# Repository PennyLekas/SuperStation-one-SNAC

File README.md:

# SuperStation-one-SNAC
THIS PROJECT IS UNTESTED

An experimental SNAC breakout for the Retro Remake SuperStation one.

This project consists of 2 PCBs. One to break the PSX port out into a JST connector and another to receive the borken out PSX control lines and convert them to the USB3.0 SNAC port. 

The SNAC adapter has level shift built in for 5V and 3.3V controllers.

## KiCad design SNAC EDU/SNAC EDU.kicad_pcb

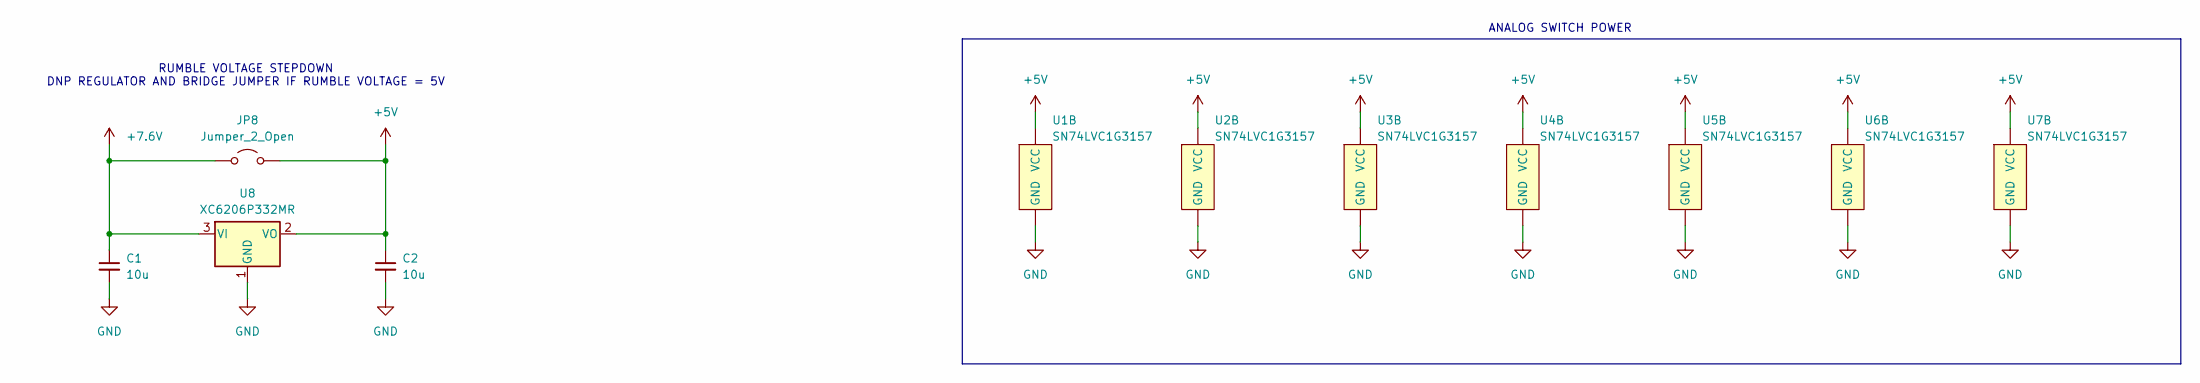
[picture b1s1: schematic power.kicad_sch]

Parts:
C1, C2: 10u; C_0603_1608Metric
JP8: Jumper_2_Open; SolderJumper-2_P1.3mm_Open_Pad1.0x1.5mm
U1, U2, U3, U4, U5, U6, U7: SN74LVC1G3157; TSOT-23-6
U8: XC6206P332MR; SOT-23-3

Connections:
+5V: C2.1, JP8.2 (B), U1.5 (VCC), U2.5 (VCC), U3.5 (VCC), U4.5 (VCC), U5.5 (VCC), U6.5 (VCC), U7.5 (VCC), U8.2 (VO); also elsewhere on the board
+7.6V: C1.1, JP8.1 (A), U8.3 (VI); also elsewhere on the board
GND: C1.2, C2.2, U1.2 (GND), U2.2 (GND), U3.2 (GND), U4.2 (GND), U5.2 (GND), U6.2 (GND), U7.2 (GND), U8.1 (GND); also elsewhere on the board

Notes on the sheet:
RUMBLE VOLTAGE STEPDOWN DNP REGULATOR AND BRIDGE JUMPER IF RUMBLE VOLTAGE = 5V
ANALOG SWITCH POWER

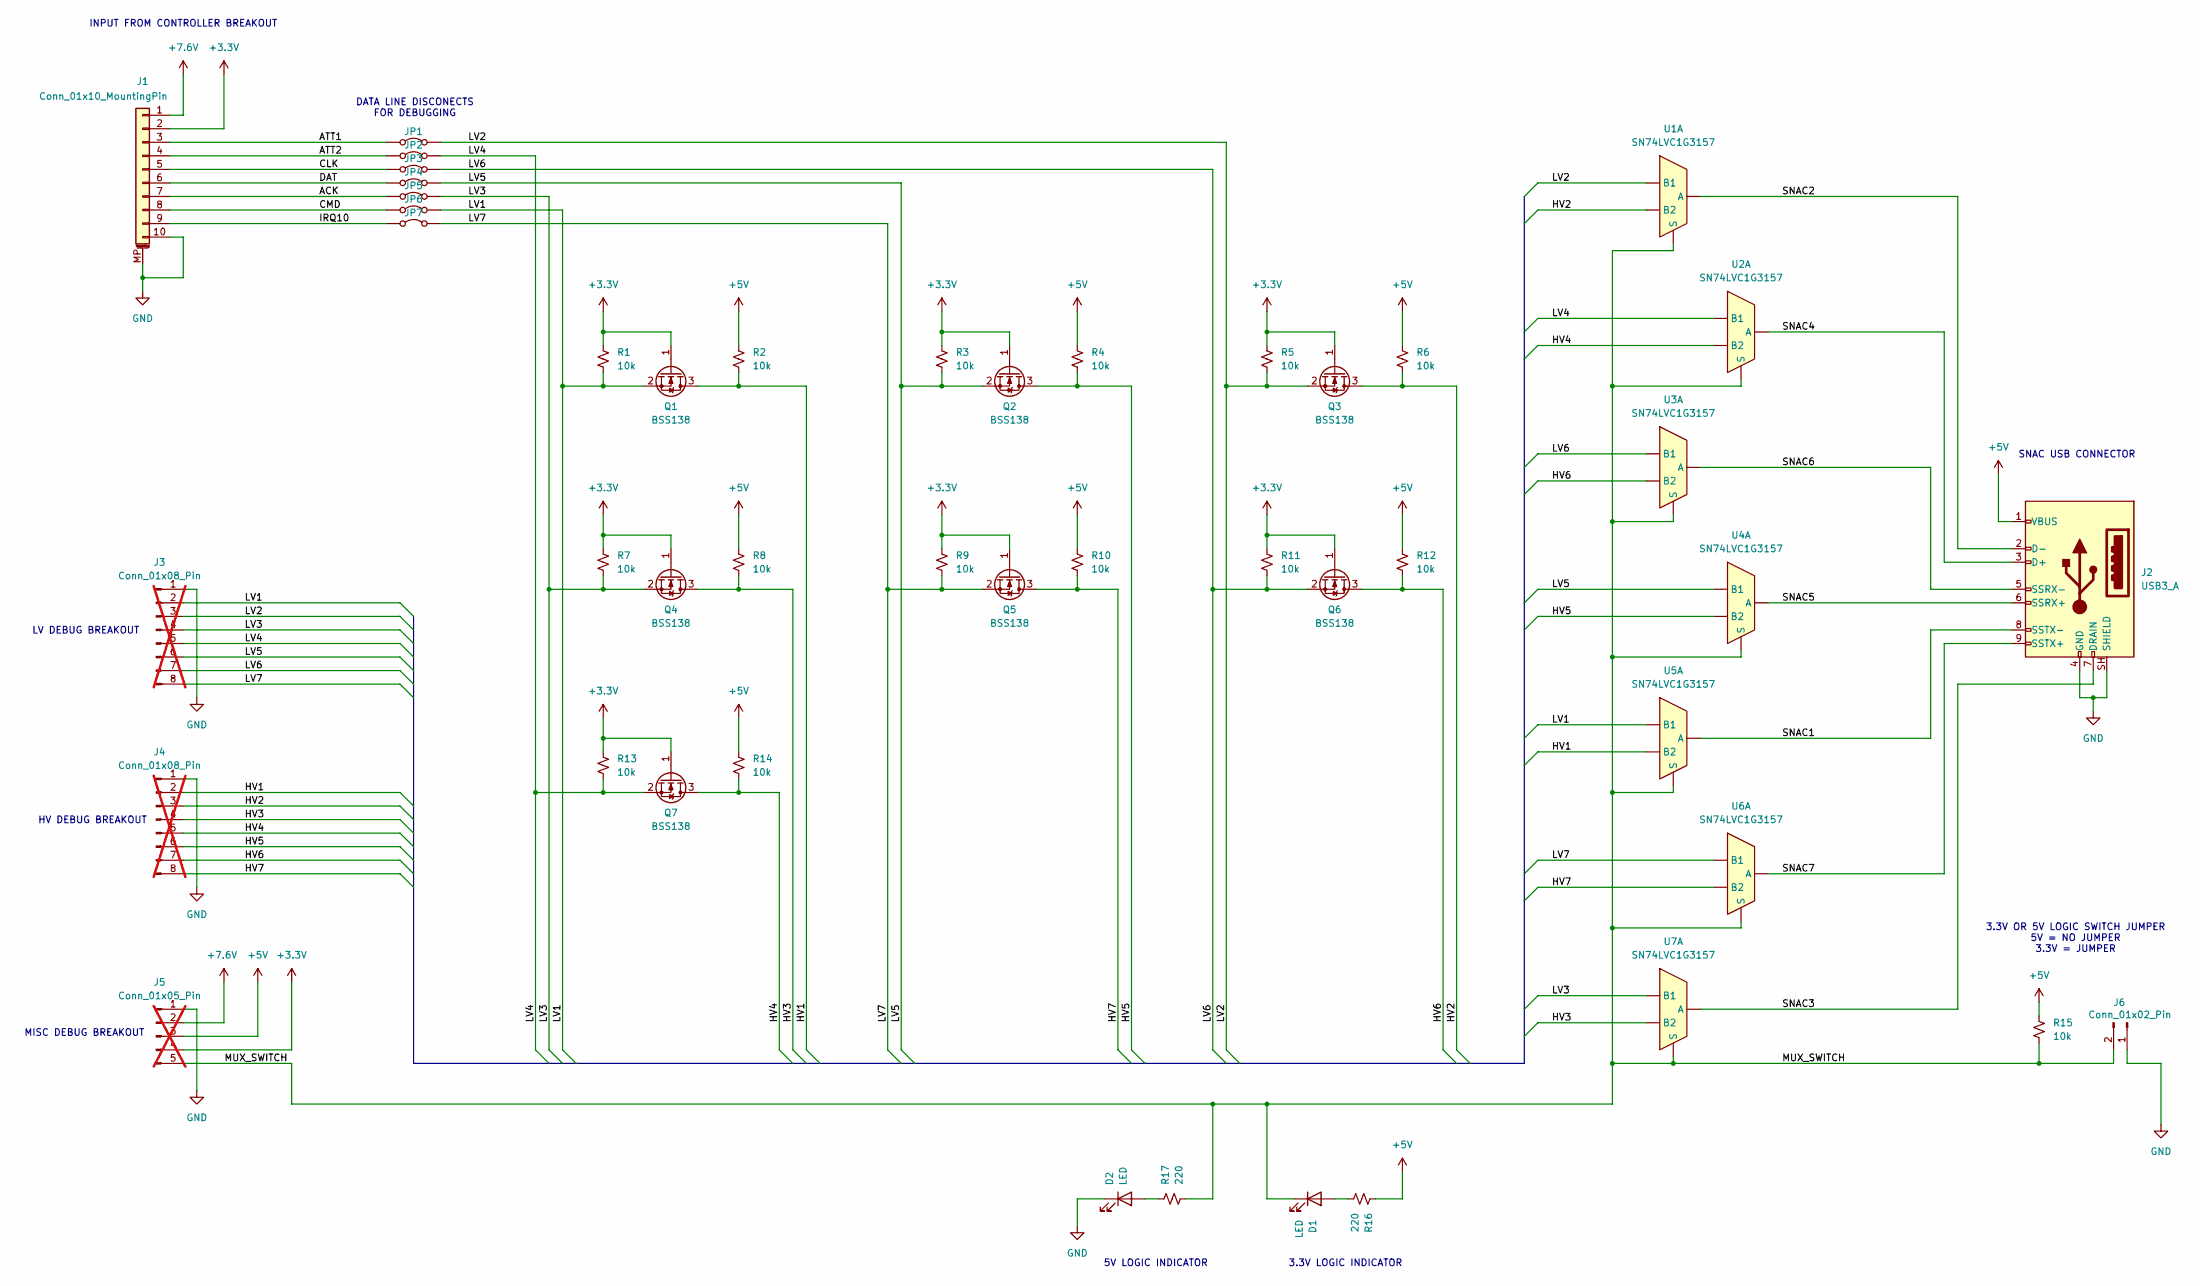
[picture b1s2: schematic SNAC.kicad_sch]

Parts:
D1, D2: LED; LED_0603_1608Metric
J1: Conn_01x10_MountingPin; JST_PH_S10B-PH-SM4-TB_1x10-1MP_P2.00mm_Horizontal
J2: USB3_A; USB3_A_Receptacle_Wuerth_692122030100
J3, J4: Conn_01x08_Pin; PinHeader_1x08_P2.54mm_Vertical; not fitted
J5: Conn_01x05_Pin; PinHeader_1x05_P2.54mm_Vertical; not fitted
J6: Conn_01x02_Pin; PinHeader_1x02_P2.54mm_Vertical
JP1, JP2, JP3, JP4, JP5, JP6, JP7: Jumper_2_Bridged; SolderJumper-2_P1.3mm_Bridged_Pad1.0x1.5mm
Q1, Q2, Q3, Q4, Q5, Q6, Q7: BSS138; SOT-23
R1, R2, R3, R4, R5, R6, R7, R8, R9, R10, R11, R12, R13, R14, R15: 10k; R_0603_1608Metric
R16, R17: 220; R_0603_1608Metric
U1, U2, U3, U4, U5, U6, U7: SN74LVC1G3157; TSOT-23-6

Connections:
+3.3V: J1.2, J5.4, Q1.1 (G), Q2.1 (G), Q3.1 (G), Q4.1 (G), Q5.1 (G), Q6.1 (G), Q7.1 (G), R1.1, R3.1, R5.1, R7.1, R9.1, R11.1, R13.1
+5V: J2.1 (VBUS), J5.3, R2.1, R4.1, R6.1, R8.1, R10.1, R12.1, R14.1, R15.2, R16.1; also elsewhere on the board
+7.6V: J1.1, J5.2; also elsewhere on the board
/SNAC/ACK: J1.7, JP5.1 (A)
/SNAC/ATT1: J1.3, JP1.1 (A)
/SNAC/ATT2: J1.4, JP2.1 (A)
/SNAC/CLK: J1.5, JP3.1 (A)
/SNAC/CMD: J1.8, JP6.1 (A)
/SNAC/DAT: J1.6, JP4.1 (A)
/SNAC/HV1: J4.2, Q1.3 (D), R2.2, U5.1 (B2)
/SNAC/HV2: J4.3, Q3.3 (D), R6.2, U1.1 (B2)
/SNAC/HV3: J4.4, Q4.3 (D), R8.2, U7.1 (B2)
/SNAC/HV4: J4.5, Q7.3 (D), R14.2, U2.1 (B2)
/SNAC/HV5: J4.6, Q2.3 (D), R4.2, U4.1 (B2)
/SNAC/HV6: J4.7, Q6.3 (D), R12.2, U3.1 (B2)
/SNAC/HV7: J4.8, Q5.3 (D), R10.2, U6.1 (B2)
/SNAC/IRQ10: J1.9, JP7.1 (A)
/SNAC/LV1: J3.2, JP6.2 (B), Q1.2 (S), R1.2, U5.3 (B1)
/SNAC/LV2: J3.3, JP1.2 (B), Q3.2 (S), R5.2, U1.3 (B1)
/SNAC/LV3: J3.4, JP5.2 (B), Q4.2 (S), R7.2, U7.3 (B1)
/SNAC/LV4: J3.5, JP2.2 (B), Q7.2 (S), R13.2, U2.3 (B1)
/SNAC/LV5: J3.6, JP4.2 (B), Q2.2 (S), R3.2, U4.3 (B1)
/SNAC/LV6: J3.7, JP3.2 (B), Q6.2 (S), R11.2, U3.3 (B1)
/SNAC/LV7: J3.8, JP7.2 (B), Q5.2 (S), R9.2, U6.3 (B1)
/SNAC/MUX_SWITCH: D1.1 (K), J5.5, J6.2, R15.1, R17.2, U1.6 (S), U2.6 (S), U3.6 (S), U4.6 (S), U5.6 (S), U6.6 (S), U7.6 (S)
/SNAC/SNAC1: J2.8 (SSTX-), U5.4 (A)
/SNAC/SNAC2: J2.2 (D-), U1.4 (A)
/SNAC/SNAC3: J2.7 (DRAIN), U7.4 (A)
/SNAC/SNAC4: J2.3 (D+), U2.4 (A)
/SNAC/SNAC5: J2.6 (SSRX+), U4.4 (A)
/SNAC/SNAC6: J2.5 (SSRX-), U3.4 (A)
/SNAC/SNAC7: J2.9 (SSTX+), U6.4 (A)
GND: D2.1 (K), J1.10, J1.MP (MountPin), J2.4 (GND), J2.SH (SHIELD), J3.1, J4.1, J5.1, J6.1; also elsewhere on the board
unnamed: D1.2 (A), R16.2
unnamed: D2.2 (A), R17.1

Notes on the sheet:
LV DEBUG BREAKOUT
HV DEBUG BREAKOUT
DATA LINE DISCONECTS FOR DEBUGGING
INPUT FROM CONTROLLER BREAKOUT
SNAC USB CONNECTOR
MISC DEBUG BREAKOUT
3.3V LOGIC INDICATOR
5V LOGIC INDICATOR
3.3V OR 5V LOGIC SWITCH JUMPER 5V = NO JUMPER 3.3V = JUMPER

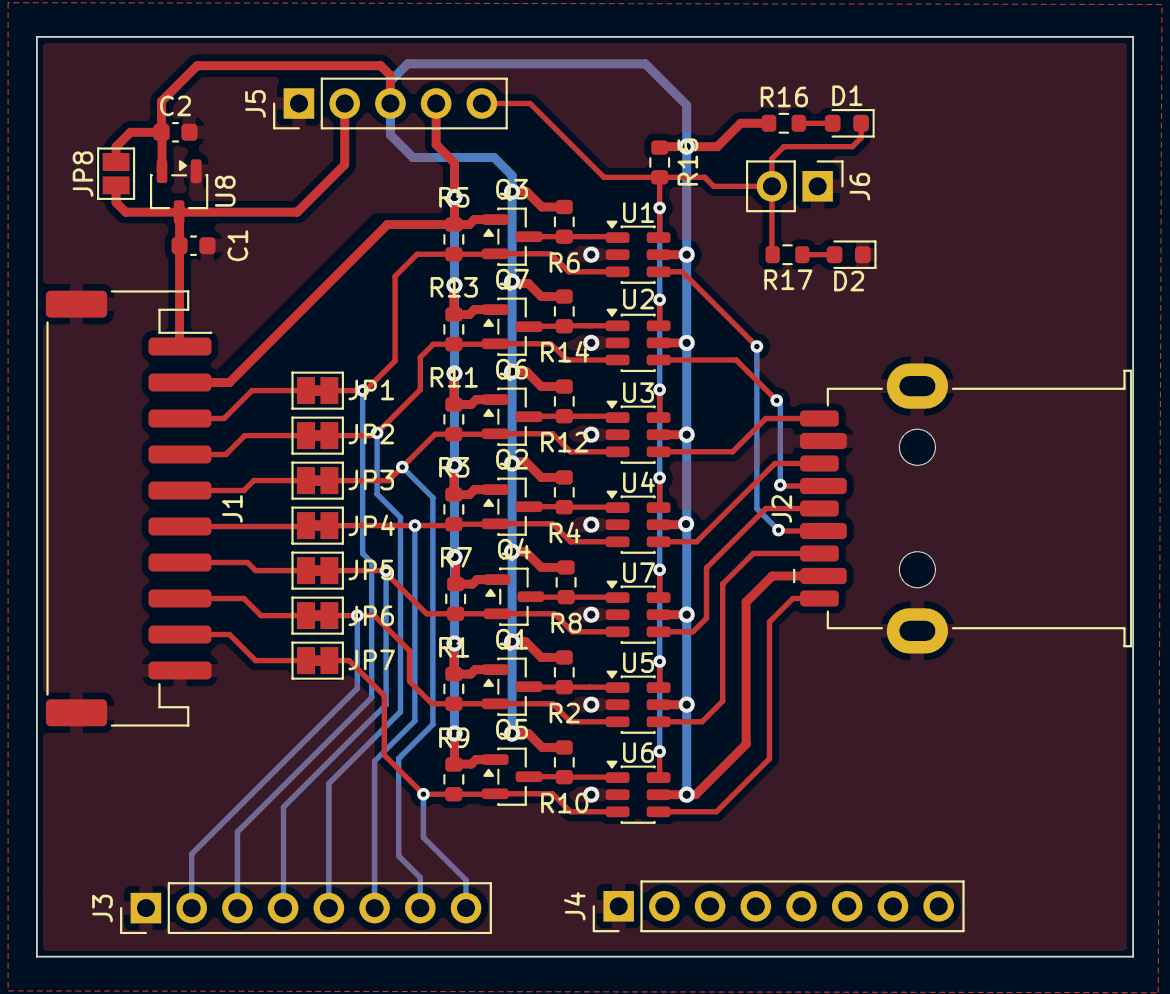
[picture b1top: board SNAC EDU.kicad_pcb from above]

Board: 2 copper layers, 60.9 x 51.1 mm, 50 parts (0 on the bottom side), 35 nets.

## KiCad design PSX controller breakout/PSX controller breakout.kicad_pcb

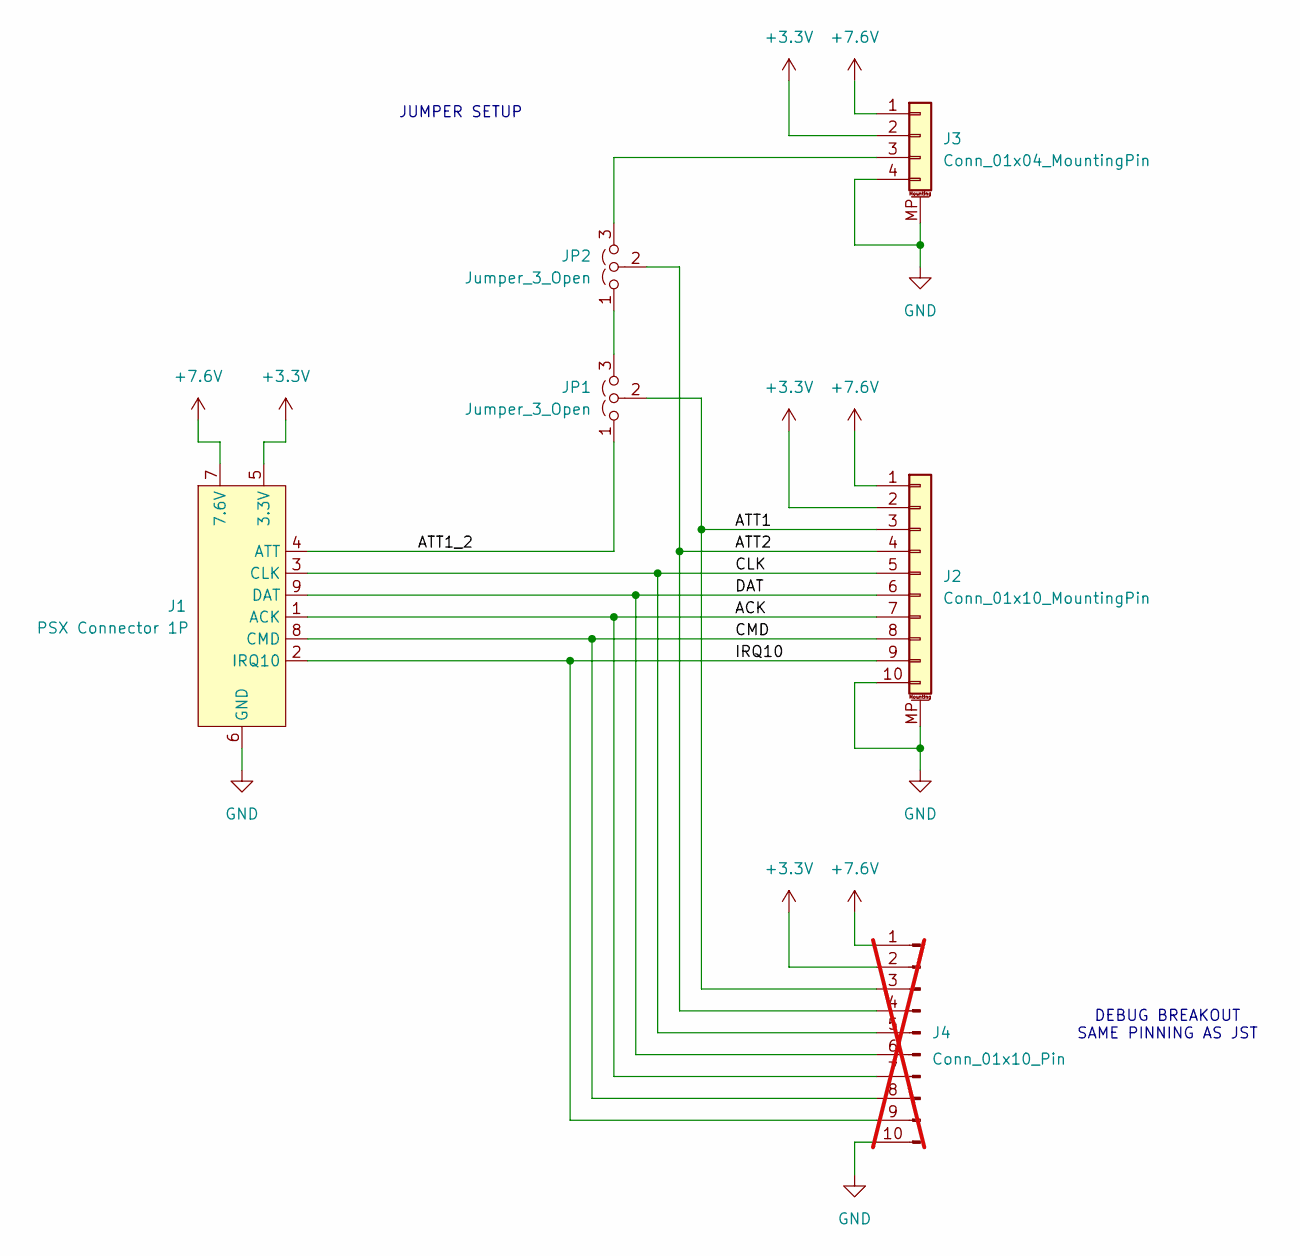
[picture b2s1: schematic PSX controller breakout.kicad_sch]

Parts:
J1: PSX Connector 1P
J2: Conn_01x10_MountingPin; JST_PH_S10B-PH-SM4-TB_1x10-1MP_P2.00mm_Horizontal
J3: Conn_01x04_MountingPin; JST_PH_S4B-PH-SM4-TB_1x04-1MP_P2.00mm_Horizontal
J4: Conn_01x10_Pin; PinSocket_1x10_P2.54mm_Vertical; not fitted
JP1, JP2: Jumper_3_Open; SolderJumper-3_P1.3mm_Open_Pad1.0x1.5mm_NumberLabels

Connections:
+3.3V: J1.5 (3.3V), J2.2, J3.2, J4.2
+7.6V: J1.7 (7.6V), J2.1, J3.1, J4.1
/ACK: J1.1 (ACK), J2.7, J4.7
/ATT1: J2.3, J4.3, JP1.2 (C)
/ATT1_2: J1.4 (ATT), JP1.1 (A)
/ATT2: J2.4, J4.4, JP2.2 (C)
/CLK: J1.3 (CLK), J2.5, J4.5
/CMD: J1.8 (CMD), J2.8, J4.8
/DAT: J1.9 (DAT), J2.6, J4.6
/IRQ10: J1.2 (IRQ10), J2.9, J4.9
GND: J1.6 (GND), J2.10, J2.MP (MountPin), J3.4, J3.MP (MountPin), J4.10
unnamed: J3.3, JP2.3 (B)
unnamed: JP1.3 (B), JP2.1 (A)

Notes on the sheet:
JUMPER SETUP
DEBUG BREAKOUT SAME PINNING AS JST

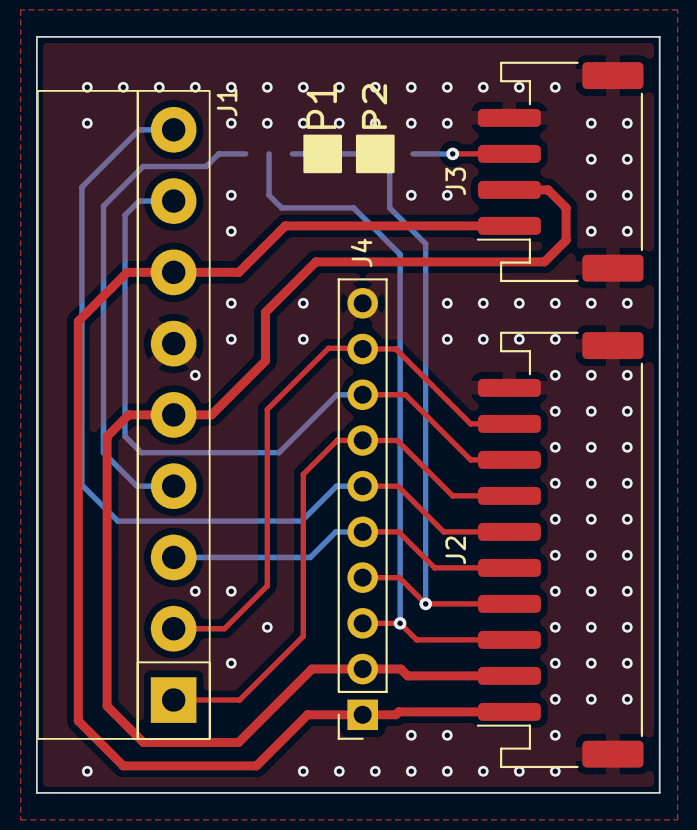
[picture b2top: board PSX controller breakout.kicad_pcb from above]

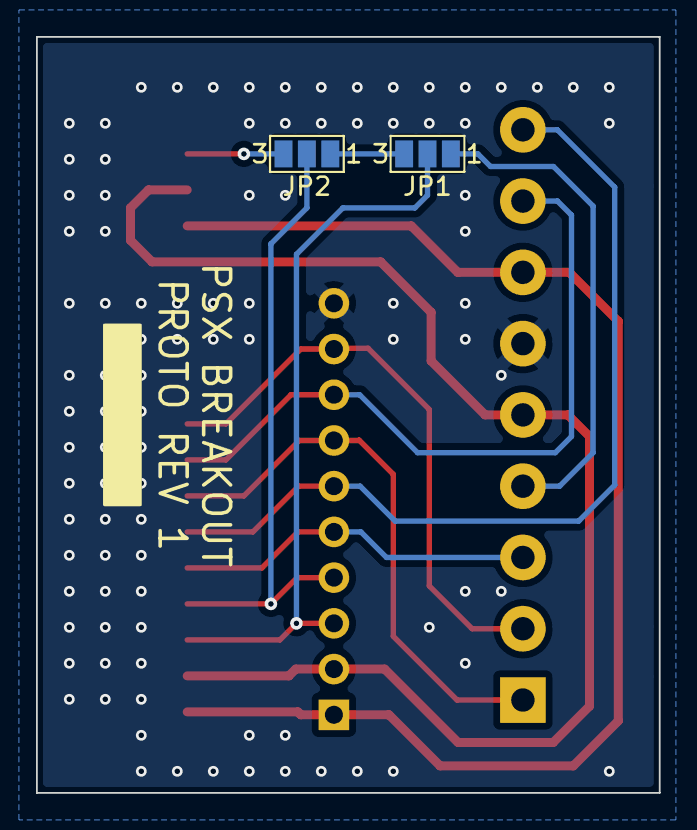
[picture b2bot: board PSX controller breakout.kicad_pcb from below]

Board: 2 copper layers, 34.6 x 42.0 mm, 6 parts (2 on the bottom side), 13 nets.

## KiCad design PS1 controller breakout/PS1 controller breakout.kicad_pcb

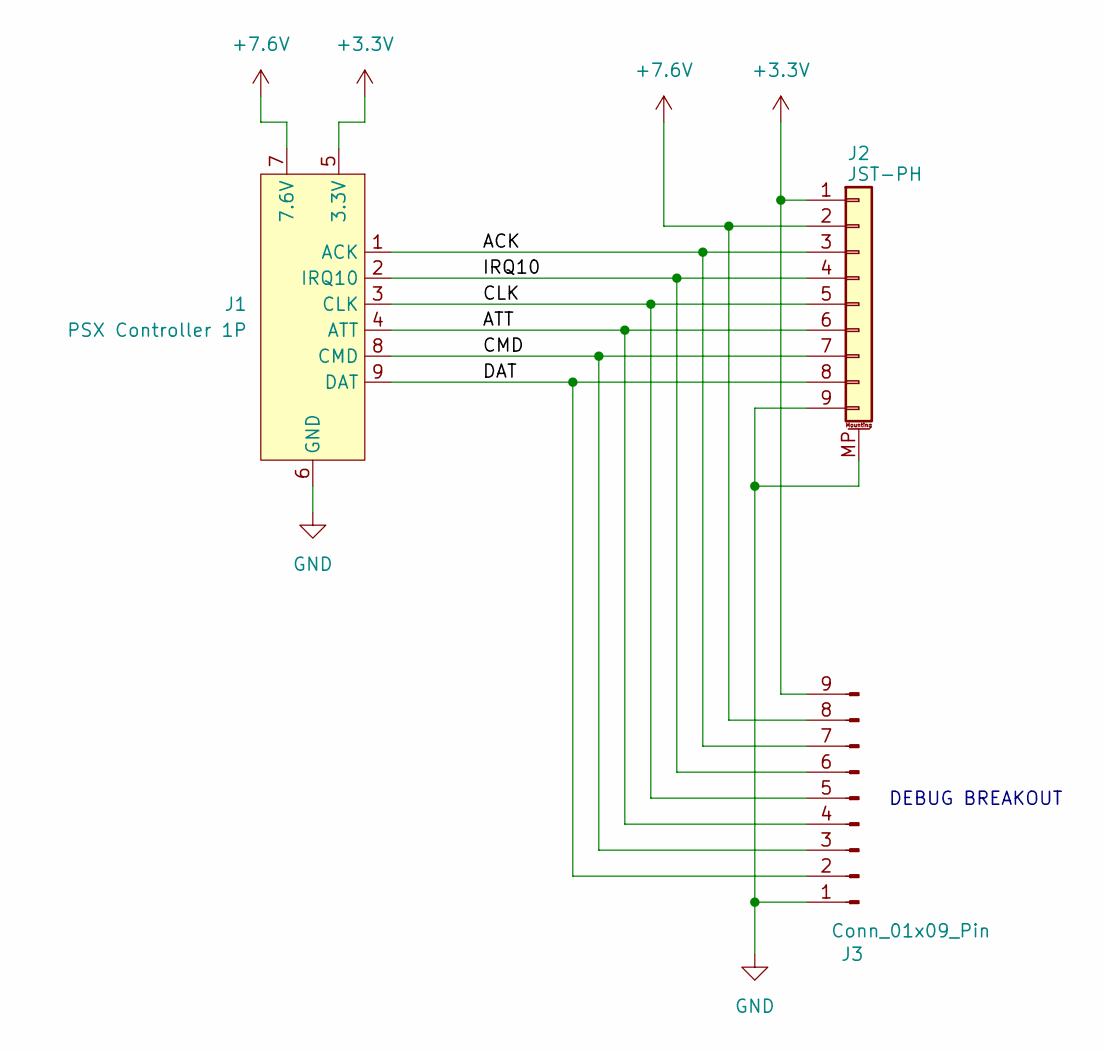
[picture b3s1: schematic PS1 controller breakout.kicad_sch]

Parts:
J1: PSX Controller 1P; PlayStation 1P
J2: JST-PH; JST_PH_S9B-PH-SM4-TB_1x09-1MP_P2.00mm_Horizontal
J3: Conn_01x09_Pin; PinHeader_1x09_P2.54mm_Vertical

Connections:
+3.3V: J1.5 (3.3V), J2.1, J3.9
+7.6V: J1.7 (7.6V), J2.2, J3.8
/ACK: J1.1 (ACK), J2.3, J3.7
/ATT: J1.4 (ATT), J2.6, J3.4
/CLK: J1.3 (CLK), J2.5, J3.5
/CMD: J1.8 (CMD), J2.7, J3.3
/DAT: J1.9 (DAT), J2.8, J3.2
/IRQ10: J1.2 (IRQ10), J2.4, J3.6
GND: J1.6 (GND), J2.9, J2.MP (MountPin), J3.1

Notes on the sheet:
DEBUG BREAKOUT

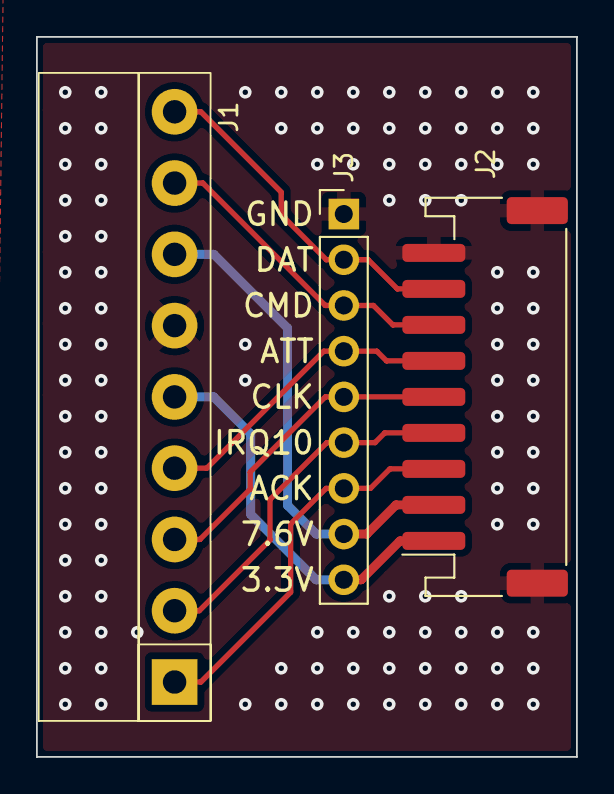
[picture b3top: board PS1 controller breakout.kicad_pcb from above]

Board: 2 copper layers, 30.0 x 40.0 mm, 3 parts (0 on the bottom side), 9 nets.

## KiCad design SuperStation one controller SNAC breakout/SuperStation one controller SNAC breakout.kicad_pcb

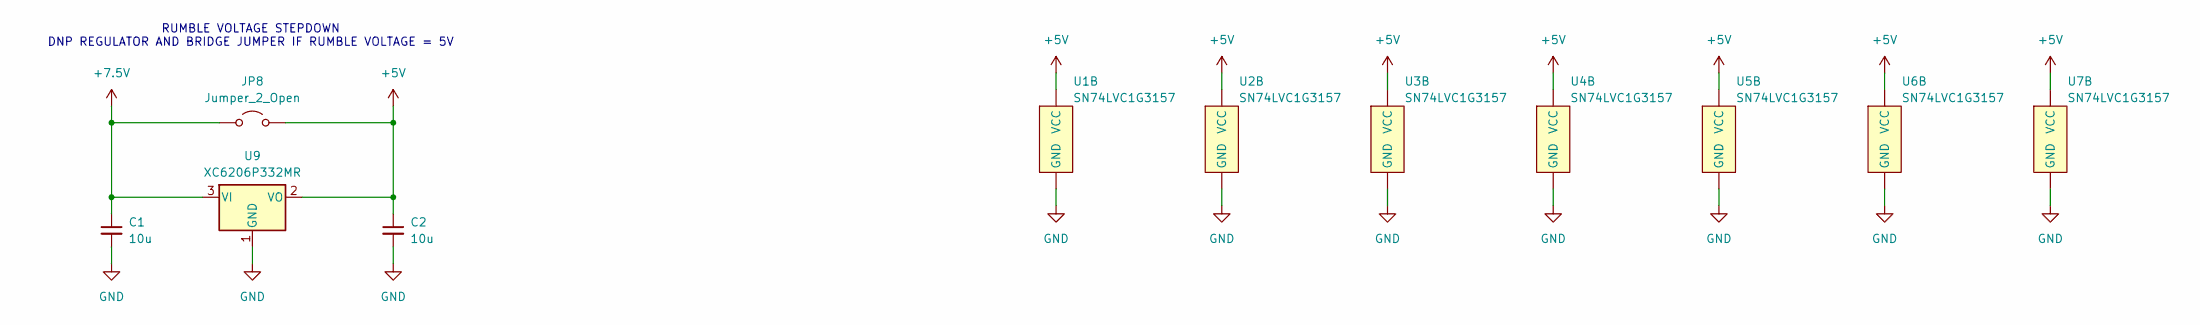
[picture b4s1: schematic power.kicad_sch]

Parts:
C1, C2: 10u; C_0603_1608Metric
JP8: Jumper_2_Open; SolderJumper-2_P1.3mm_Open_Pad1.0x1.5mm
U1, U2, U3, U4, U5, U6, U7: SN74LVC1G3157; TSOT-23-6
U9: XC6206P332MR; SOT-23-3

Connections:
+5V: C2.1, JP8.2 (B), U1.5 (VCC), U2.5 (VCC), U3.5 (VCC), U4.5 (VCC), U5.5 (VCC), U6.5 (VCC), U7.5 (VCC), U9.2 (VO); also elsewhere on the board
+7.5V: C1.1, JP8.1 (A), U9.3 (VI); also elsewhere on the board
GND: C1.2, C2.2, U1.2 (GND), U2.2 (GND), U3.2 (GND), U4.2 (GND), U5.2 (GND), U6.2 (GND), U7.2 (GND), U9.1 (GND); also elsewhere on the board

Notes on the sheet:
RUMBLE VOLTAGE STEPDOWN DNP REGULATOR AND BRIDGE JUMPER IF RUMBLE VOLTAGE = 5V

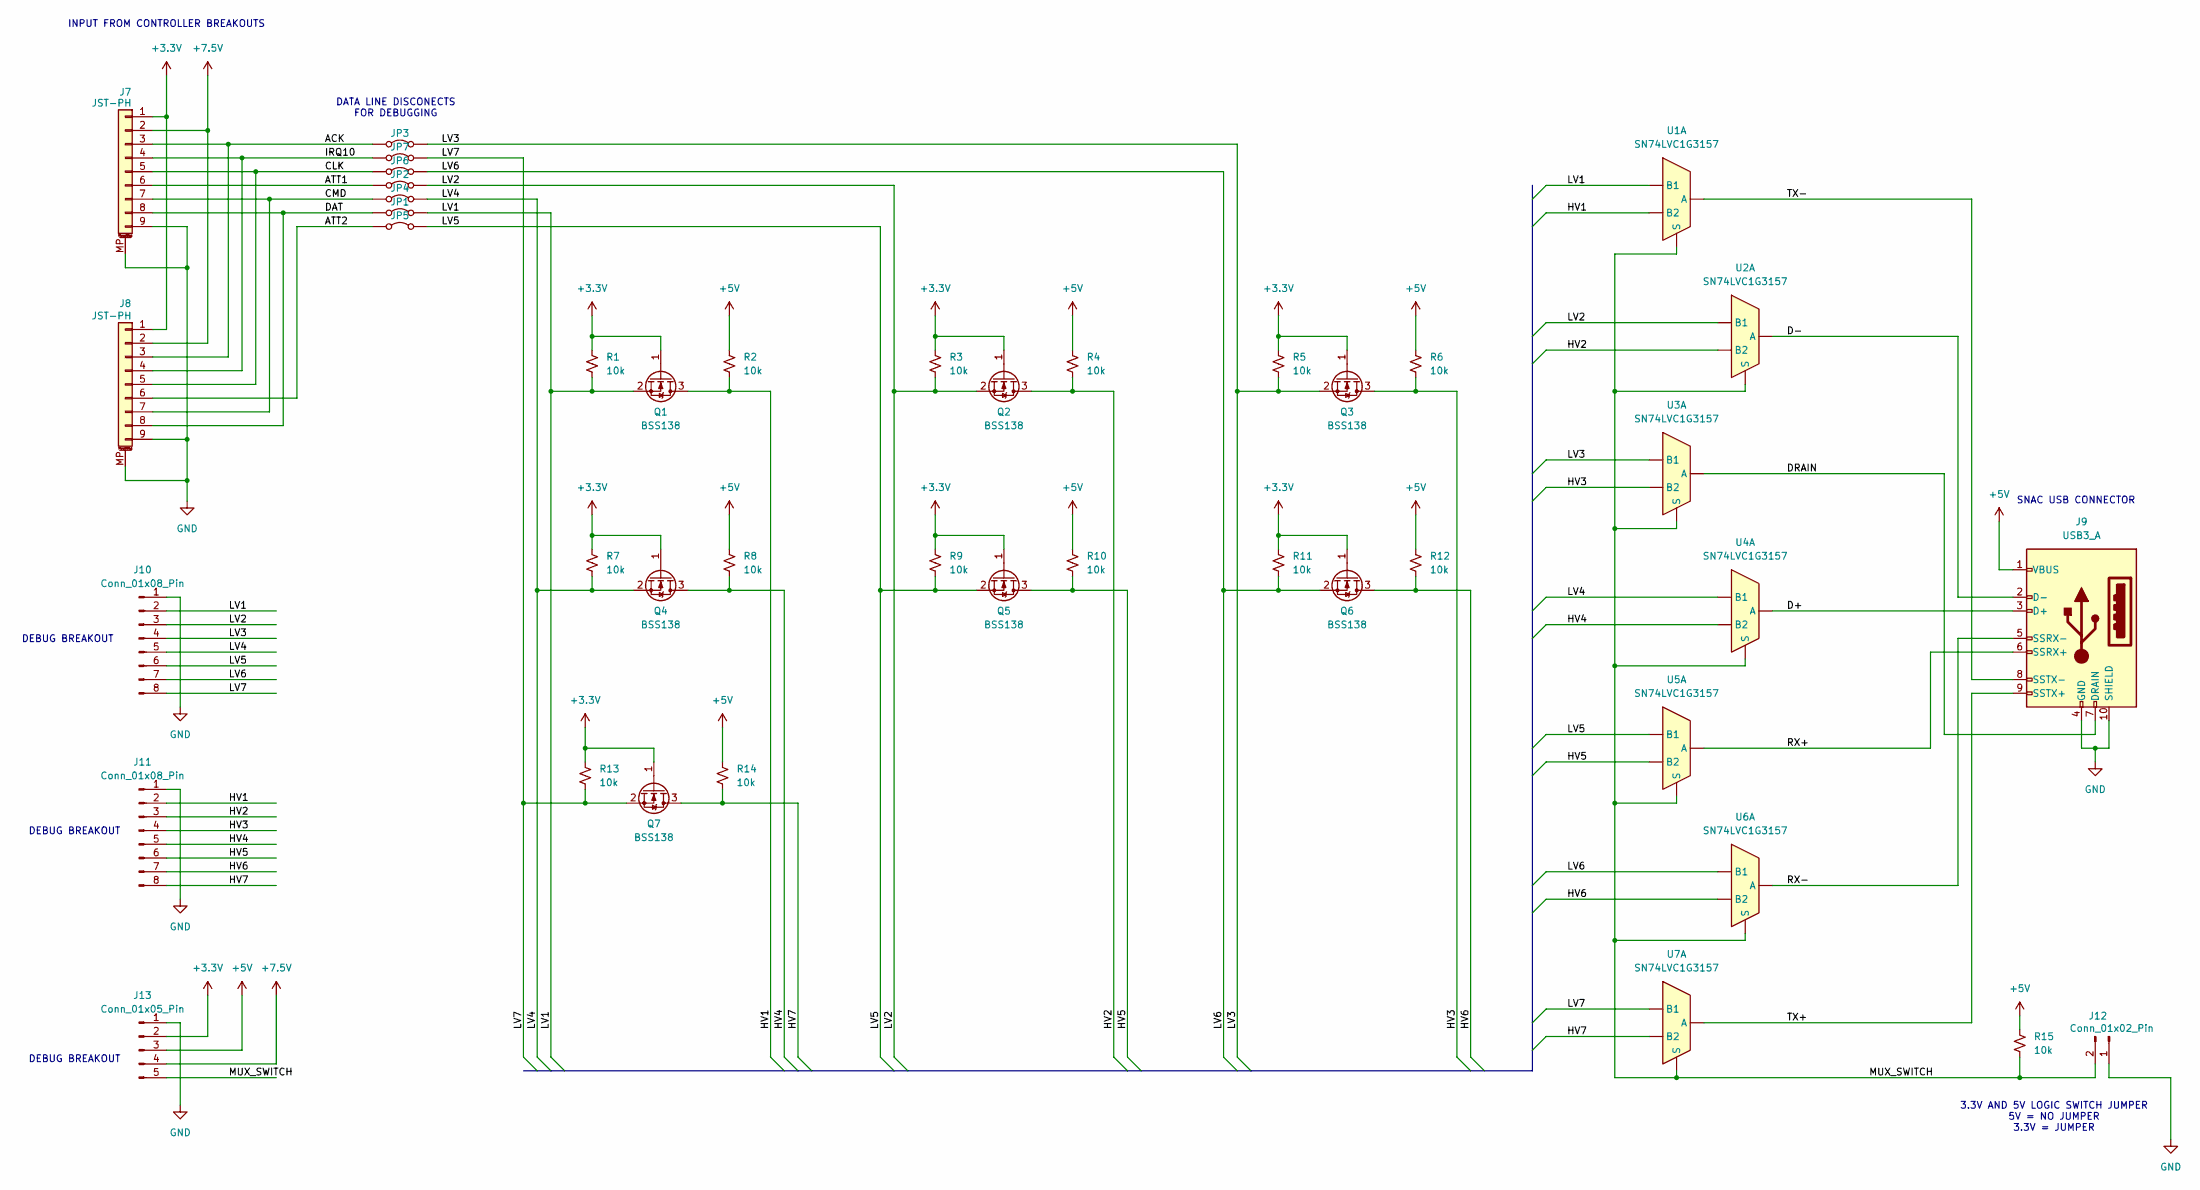
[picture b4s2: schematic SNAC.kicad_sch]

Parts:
J7, J8: JST-PH; JST_PH_S9B-PH-SM4-TB_1x09-1MP_P2.00mm_Horizontal
J9: USB3_A; USB3_A_Receptacle_Wuerth_692122030100
J10, J11: Conn_01x08_Pin; PinHeader_1x08_P2.54mm_Vertical
J12: Conn_01x02_Pin; PinHeader_1x02_P2.54mm_Vertical
J13: Conn_01x05_Pin; PinHeader_1x05_P2.54mm_Vertical
JP1, JP2, JP3, JP4, JP5, JP6, JP7: Jumper_2_Bridged; SolderJumper-2_P1.3mm_Bridged_Pad1.0x1.5mm
Q1, Q2, Q3, Q4, Q5, Q6, Q7: BSS138; SOT-23
R1, R2, R3, R4, R5, R6, R7, R8, R9, R10, R11, R12, R13, R14, R15: 10k; R_0603_1608Metric
U1, U2, U3, U4, U5, U6, U7: SN74LVC1G3157; TSOT-23-6

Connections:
+3.3V: J7.1, J8.1, J13.2, Q1.1 (G), Q2.1 (G), Q3.1 (G), Q4.1 (G), Q5.1 (G), Q6.1 (G), Q7.1 (G), R1.1, R3.1, R5.1, R7.1, R9.1, R11.1, R13.1
+5V: J9.1 (VBUS), J13.3, R2.1, R4.1, R6.1, R8.1, R10.1, R12.1, R14.1, R15.2; also elsewhere on the board
+7.5V: J7.2, J8.2, J13.4; also elsewhere on the board
/SNAC/ACK: J7.3, J8.3, JP3.1 (A)
/SNAC/ATT1: J7.6, JP2.1 (A)
/SNAC/ATT2: J8.6, JP5.1 (A)
/SNAC/CLK: J7.5, J8.5, JP6.1 (A)
/SNAC/CMD: J7.7, J8.7, JP4.1 (A)
/SNAC/D+: J9.3 (D+), U4.4 (A)
/SNAC/D-: J9.2 (D-), U2.4 (A)
/SNAC/DAT: J7.8, J8.8, JP1.1 (A)
/SNAC/DRAIN: J9.7 (DRAIN), U3.4 (A)
/SNAC/HV1: J11.2, Q1.3 (D), R2.2, U1.1 (B2)
/SNAC/HV2: J11.3, Q2.3 (D), R4.2, U2.1 (B2)
/SNAC/HV3: J11.4, Q3.3 (D), R6.2, U3.1 (B2)
/SNAC/HV4: J11.5, Q4.3 (D), R8.2, U4.1 (B2)
/SNAC/HV5: J11.6, Q5.3 (D), R10.2, U5.1 (B2)
/SNAC/HV6: J11.7, Q6.3 (D), R12.2, U6.1 (B2)
/SNAC/HV7: J11.8, Q7.3 (D), R14.2, U7.1 (B2)
/SNAC/IRQ10: J7.4, J8.4, JP7.1 (A)
/SNAC/LV1: J10.2, JP1.2 (B), Q1.2 (S), R1.2, U1.3 (B1)
/SNAC/LV2: J10.3, JP2.2 (B), Q2.2 (S), R3.2, U2.3 (B1)
/SNAC/LV3: J10.4, JP3.2 (B), Q3.2 (S), R5.2, U3.3 (B1)
/SNAC/LV4: J10.5, JP4.2 (B), Q4.2 (S), R7.2, U4.3 (B1)
/SNAC/LV5: J10.6, JP5.2 (B), Q5.2 (S), R9.2, U5.3 (B1)
/SNAC/LV6: J10.7, JP6.2 (B), Q6.2 (S), R11.2, U6.3 (B1)
/SNAC/LV7: J10.8, JP7.2 (B), Q7.2 (S), R13.2, U7.3 (B1)
/SNAC/MUX_SWITCH: J12.2, J13.5, R15.1, U1.6 (S), U2.6 (S), U3.6 (S), U4.6 (S), U5.6 (S), U6.6 (S), U7.6 (S)
/SNAC/RX+: J9.6 (SSRX+), U5.4 (A)
/SNAC/RX-: J9.5 (SSRX-), U6.4 (A)
/SNAC/TX+: J9.9 (SSTX+), U7.4 (A)
/SNAC/TX-: J9.8 (SSTX-), U1.4 (A)
GND: J7.9, J7.MP (MountPin), J8.9, J8.MP (MountPin), J9.4 (GND), J9.10 (SHIELD), J10.1, J11.1, J12.1, J13.1; also elsewhere on the board

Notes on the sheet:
DEBUG BREAKOUT
DATA LINE DISCONECTS FOR DEBUGGING
INPUT FROM CONTROLLER BREAKOUTS
SNAC USB CONNECTOR
3.3V AND 5V LOGIC SWITCH JUMPER 5V = NO JUMPER 3.3V = JUMPER

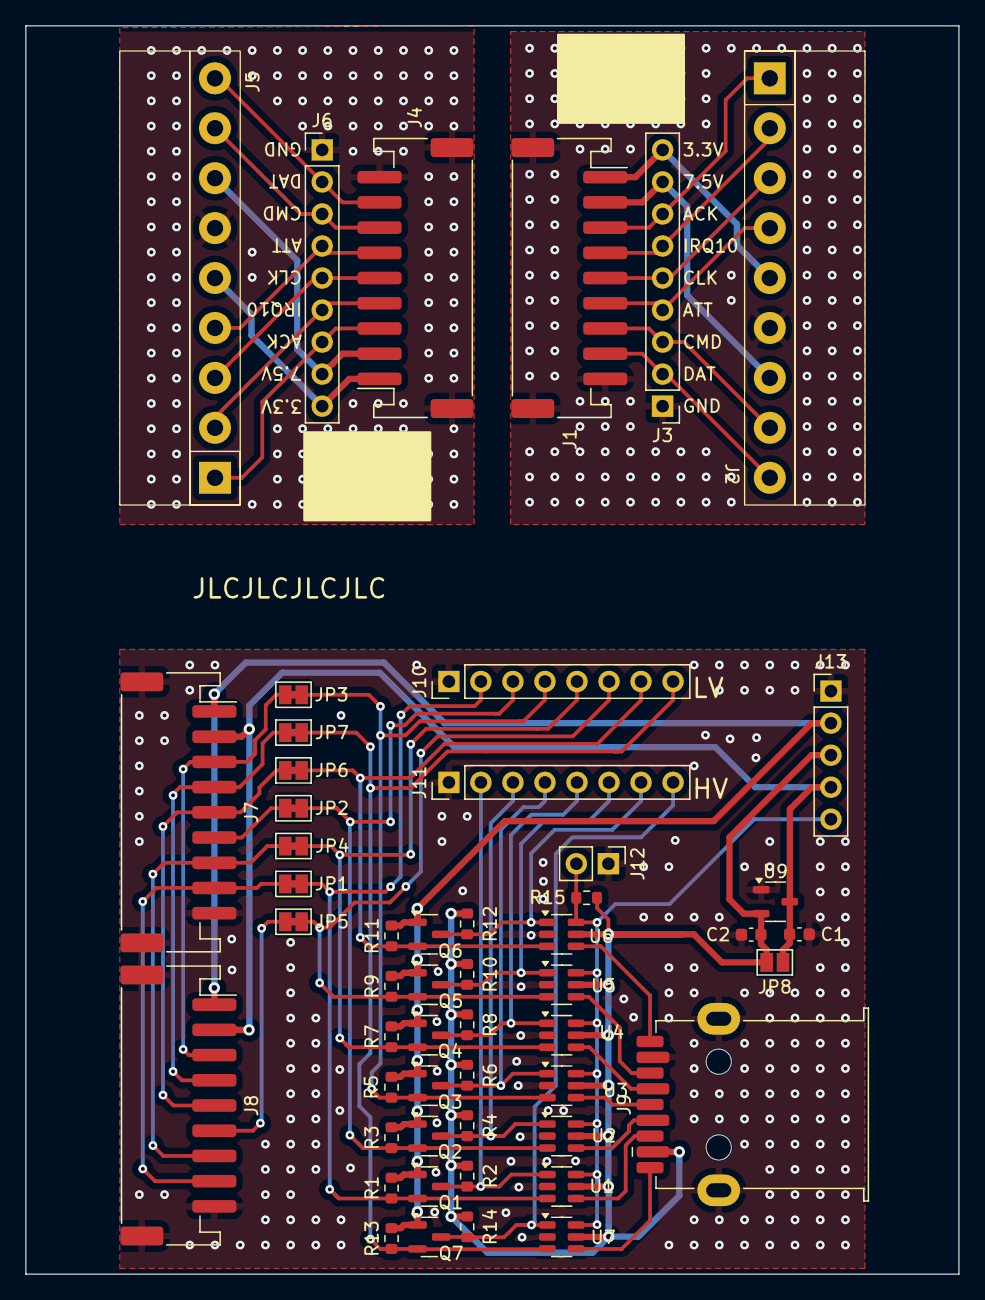
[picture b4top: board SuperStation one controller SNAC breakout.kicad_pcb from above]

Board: 2 copper layers, 74.0 x 99.0 mm, 53 parts (0 on the bottom side), 51 nets.

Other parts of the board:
J1, J4: JST-PH; JST_PH_S9B-PH-SM4-TB_1x09-1MP_P2.00mm_Horizontal
J2, J5: PlayStation Con 1P; PlayStation 1P
J3, J6: Conn_01x09_Pin; PinHeader_1x09_P2.54mm_Vertical

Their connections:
+3.3V_P1: J1.1, J2.5 (3.3V), J3.9
+3.3V_P2: J4.1, J5.5 (3.3V), J6.9
+7.5V_P1: J1.2, J2.7 (7.6V), J3.8
+7.5V_P2: J4.2, J5.7 (7.6V), J6.8
/PS Input Breakout/ACK_P1: J1.3, J2.1 (ACK), J3.7
/PS Input Breakout/ACK_P2: J4.3, J5.1 (ACK), J6.7
/PS Input Breakout/ATT_P1: J1.6, J2.4 (ATT), J3.4
/PS Input Breakout/ATT_P2: J4.6, J5.4 (ATT), J6.4
/PS Input Breakout/CLK_P1: J1.5, J2.3 (CLK), J3.5
/PS Input Breakout/CLK_P2: J4.5, J5.3 (CLK), J6.5
/PS Input Breakout/CMD_P1: J1.7, J2.8 (CMD), J3.3
/PS Input Breakout/CMD_P2: J4.7, J5.8 (CMD), J6.3
/PS Input Breakout/DAT_P1: J1.8, J2.9 (DAT), J3.2
/PS Input Breakout/DAT_P2: J4.8, J5.9 (DAT), J6.2
/PS Input Breakout/IRQ10_P1: J1.4, J2.2 (IRQ10), J3.6
/PS Input Breakout/IRQ10_P2: J4.4, J5.2 (IRQ10), J6.6
GND_P1: J1.9, J1.MP (MountPin), J2.6 (GND), J3.1
GND_P2: J4.9, J4.MP (MountPin), J5.6 (GND), J6.1

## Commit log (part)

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2025-01-28 added reference material
2025-01-28 completed initial schematic and started layout
2025-02-02 continued work on schematic. Added connector breakouts and muxing for 3.3v and 5v SNACs
2025-02-02 added power sheet to schematic and started rough pcb placement
2025-02-02 board layout and added debug breakouts for all signals
2025-02-03 completed board layout
2025-02-04 replaced voltage regulator with a cheaper and smaller alternative. The same that is on all opensource SNAC adapters.
2025-02-05 split the controller and levelshifter into 2 projects for easier manufacturing
2025-02-05 added connector labels and jumpers for P2 data lines
